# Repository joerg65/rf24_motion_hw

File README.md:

# rf24_motion_hw  

This is the KiCad project of RF24 Motion Sensor.

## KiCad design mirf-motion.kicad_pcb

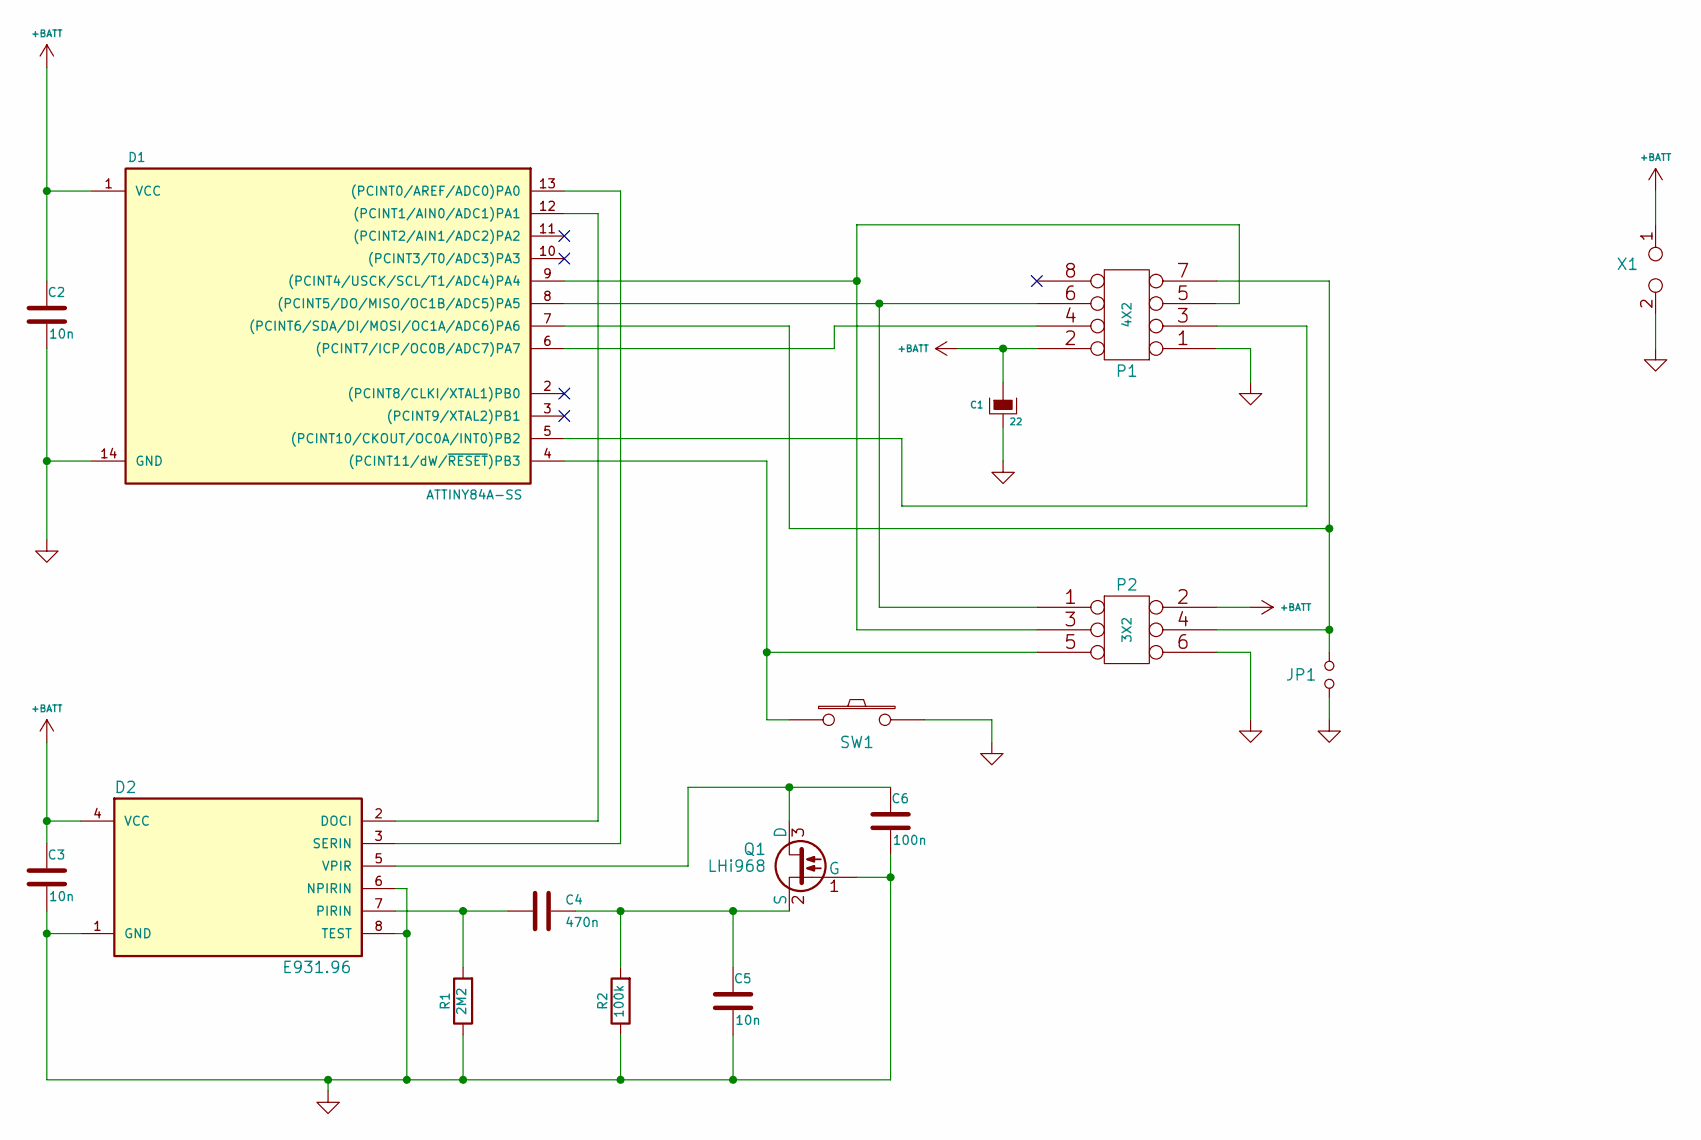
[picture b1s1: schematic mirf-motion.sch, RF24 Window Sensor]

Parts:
C1: 22; c_elec_5x4.5
C2, C3, C5: 10n; C_1206_HandSoldering
C4: 470n; C_1812_HandSoldering
C6: 100n; C_4.6_4.0_HandSoldering
D1: ATTINY84A-SS; SSOP-14
D2: E931.96; SOIC-8_3.9x4.9mm_Pitch1.27mm
JP1: Jumper_NO_Small; Pin_Header_Straight_1x02
P1: 4X2; Pin_Header_Straight_2x04
P2: 3X2; Pin_Header_Straight_2x03
Q1: LHi968; TO-43_3Pin
R1: 2M2; R_1206_HandSoldering
R2: 100k; R_1206_HandSoldering
SW1: SW_PUSH; SW_PUSH_SMALL
X1: Term-2p; TerminalBlock_Pheonix_MKDS1.5-2pol

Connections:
+BATT: C1.1, C2.1, C3.1, D1.1 (VCC), D2.4 (VCC), P1.2, P2.2, X1.1
GND: C1.2, C2.2, C3.2, C5.2, C6.2, D1.14 (GND), D2.1 (GND), D2.6 (NPIRIN), D2.8 (TEST), JP1.2, P1.1, P2.6, Q1.1 (G), R1.1, R2.1, SW1.2, X1.2
unnamed: C4.1, C5.1, Q1.2 (S), R2.2
unnamed: C4.2, D2.7 (PIRIN), R1.2
unnamed: C6.1, D2.5 (VPIR), Q1.3 (D)
unnamed: D1.4 ((PCINT11/dW/~RESET~)PB3), P2.5, SW1.1
unnamed: D1.5 ((PCINT10/CKOUT/OC0A/INT0)PB2), P1.3
unnamed: D1.6 ((PCINT7/ICP/OC0B/ADC7)PA7), P1.4
unnamed: D1.7 ((PCINT6/SDA/DI/MOSI/OC1A/ADC6)PA6), JP1.1, P1.7, P2.4
unnamed: D1.8 ((PCINT5/DO/MISO/OC1B/ADC5)PA5), P1.6, P2.1
unnamed: D1.9 ((PCINT4/USCK/SCL/T1/ADC4)PA4), P1.5, P2.3
unnamed: D1.12 ((PCINT1/AIN0/ADC1)PA1), D2.2 (DOCI)
unnamed: D1.13 ((PCINT0/AREF/ADC0)PA0), D2.3 (SERIN)

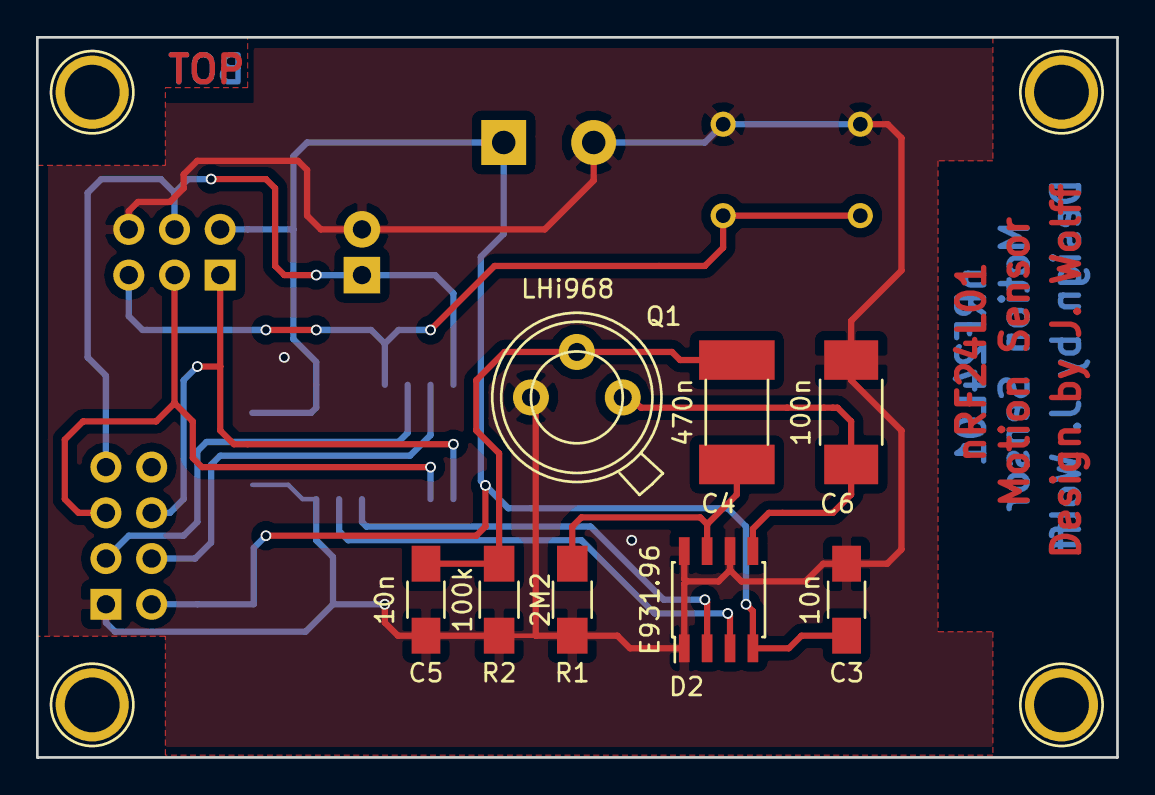
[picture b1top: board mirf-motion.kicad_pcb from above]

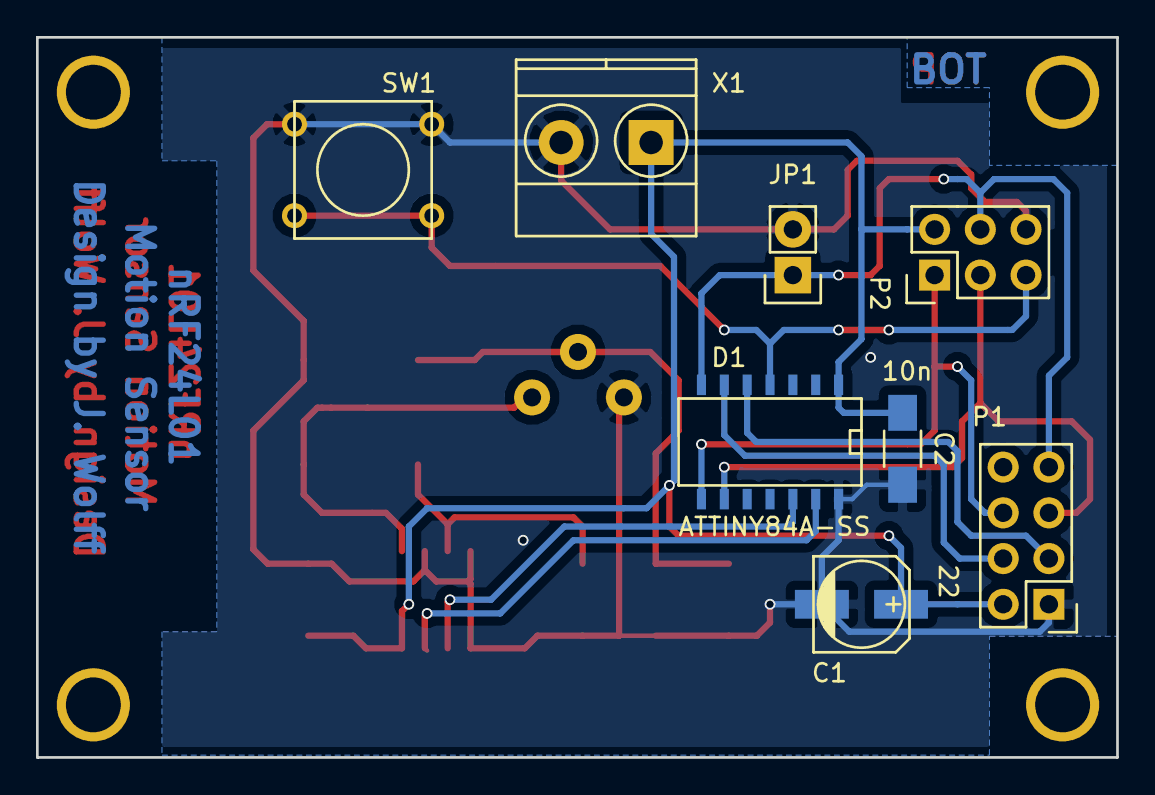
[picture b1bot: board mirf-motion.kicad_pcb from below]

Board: 2 copper layers, 60.0 x 40.0 mm, 16 parts (8 on the bottom side), 13 nets.

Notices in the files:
mirf-motion.sch:
License: see cern_ohl_v_1_2.txt
